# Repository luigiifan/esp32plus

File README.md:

# ESP32+ PROJECT

### I. Features
🔧 Fixes incorrect Boot Mode selection<br>
🔓 Compatible with <ins>ESP32 DevKit-V4 only</ins><br>
🔌 Stepdown Buck Converter MP1584 supports<br>
⚡ Includes 3.3V and 5V additional Power Expander<br>

### II. Technical Description
| Label  | Component  | I/O    | Switchable | Description |
| :------: | :-----: | :------: | :-----: | ----- |
| S1 | Pushbutton | GPIO 34 |  | Parallel with pull-up 10K Resistor to 3.3V |
| S2 | Pushbutton | GPIO 35 |  | Parallel with pull-up 10K Resistor to 3.3V |
| L1 | 3mm LED | GPIO 17 | ✅ | Series 330 ohm Resistor for current limiter, Toggle switch (IV) to enable |
| L2 | 3mm LED | GPIO 16 | ✅ | Series 330 ohm Resistor for current limiter, Toggle switch (III) to enable |
| L3 | 3mm LED | GPIO 4 | ✅ | Series 330 ohm Resistor for current limiter, Toggle switch (II) to enable |
| L4 | 3mm LED | GPIO 2 | ✅ | Series 330 ohm Resistor for current limiter, Toggle switch (I) to enable |
| SG1 | Buzzer DC | GPIO 32 | ✅ | Place (B) jumper on pins 1-2 to enable |
| DISP | OLED 128x32 | GPIO 21 (SDA) <br> GPIO 22 (SCL) | ✅ | Place (D) jumper on pins 1-2 to enable |
| C1 | Polar Capacitor | EN | | Determine ESP32 to FLASH mode upon power-up |

### III. Schematic 
🔗 [Download PDF](https://github.com/user-attachments/files/19268394/esp32_plus.pdf)

### IV. 3D Model & Drawing
<p>
  
🔗 [Download PDF](https://github.com/user-attachments/files/19269748/ESP32_PLUS_DRAWING.pdf)

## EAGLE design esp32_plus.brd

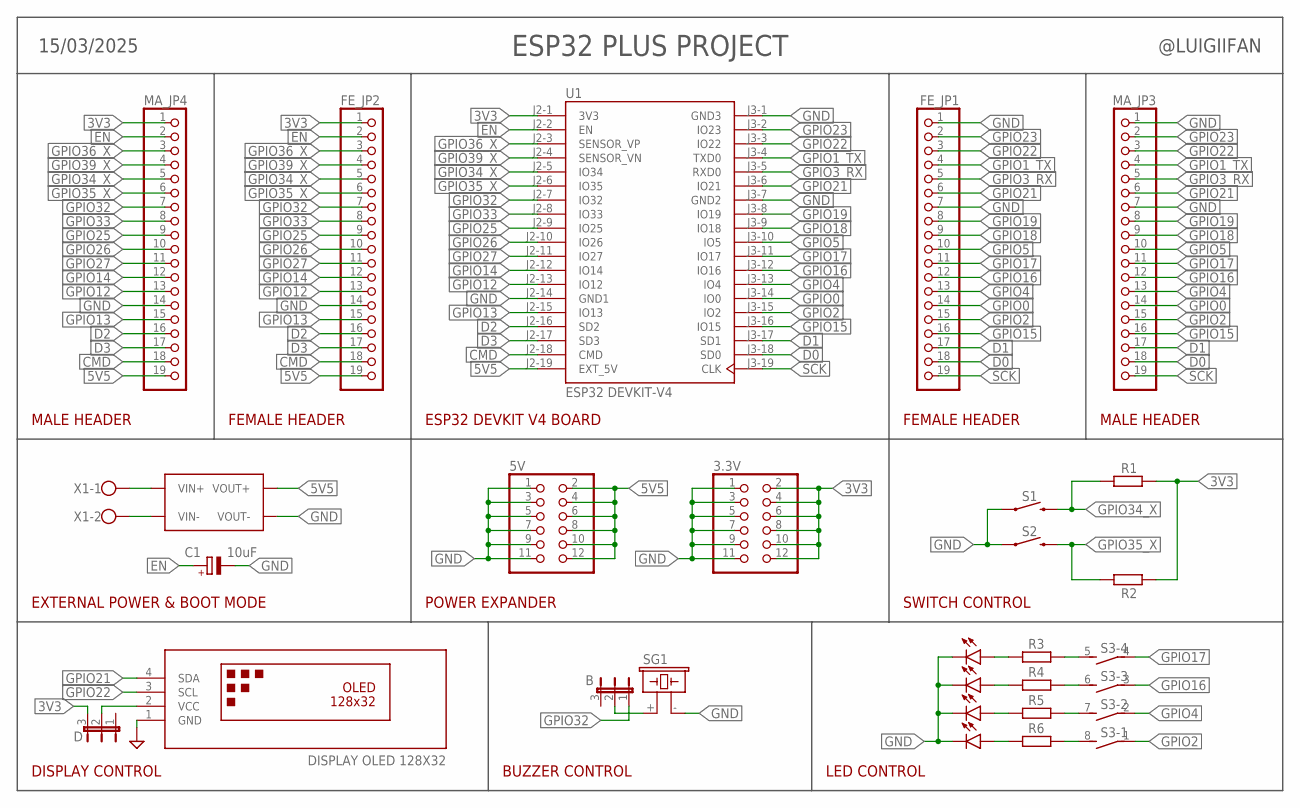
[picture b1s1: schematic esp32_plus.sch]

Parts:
3.3V, 5V: PINHD-2X6; 2X06
B: JP2E; JP2
C1: 10uF; E2,5-5
D: JP2E; JP2
FE_JP1, FE_JP2: PINHD-1X19; 1X19
L1, L2, L3, L4: LED3MM
MA_JP3, MA_JP4: PINHD-1X19; 1X19
MP1584: MP1584; DC-BRICK
R1, R2, R3, R4, R5, R6: R-EU_0207/10; 0207/10
S1, S2: MOMENTARY-SWITCH-SPST-PTH-6.0MM; TACTILE_SWITCH_PTH_6.0MM
S3: DS04E; DS-04
SG1: F/CM12P
U1: ESP32 DEVKIT-V4; MODULE_ESP32-DEVKITC-32D
U$1: DISPLAY OLED 128X32; DISPLAY-OLED-128X32
X1: W237-102

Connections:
3V3: 3.3V.2, 3.3V.4, 3.3V.6, 3.3V.8, 3.3V.10, 3.3V.12, D.3, FE_JP2.1, MA_JP4.1, R1.2, R2.2, U1.J2-1 (3V3)
5V5: 5V.2, 5V.4, 5V.6, 5V.8, 5V.10, 5V.12, FE_JP2.19, MA_JP4.19, MP1584.OUT1+ (VOUT+), MP1584.OUT2+ (VOUT+), U1.J2-19 (EXT_5V)
CMD: FE_JP2.18, MA_JP4.18, U1.J2-18 (CMD)
D0: FE_JP1.18, MA_JP3.18, U1.J3-18 (SD0)
D1: FE_JP1.17, MA_JP3.17, U1.J3-17 (SD1)
D2: FE_JP2.16, MA_JP4.16, U1.J2-16 (SD2)
D3: FE_JP2.17, MA_JP4.17, U1.J2-17 (SD3)
EN: C1.+, FE_JP2.2, MA_JP4.2, U1.J2-2 (EN)
GND: 3.3V.1, 3.3V.3, 3.3V.5, 3.3V.7, 3.3V.9, 3.3V.11, 5V.1, 5V.3, 5V.5, 5V.7, 5V.9, 5V.11, C1.-, FE_JP1.1, FE_JP1.7, FE_JP2.14, L1.K (C), L2.K (C), L3.K (C), L4.K (C), MA_JP3.1, MA_JP3.7, MA_JP4.14, MP1584.OUT1- (VOUT-), MP1584.OUT2- (VOUT-), S1.1, S2.1, SG1.- (2), U1.J2-14 (GND1), U1.J3-1 (GND3), U1.J3-7 (GND2), U$1.1 (GND)
GPIO0: FE_JP1.14, MA_JP3.14, U1.J3-14 (IO0)
GPIO1_TX: FE_JP1.4, MA_JP3.4, U1.J3-4 (TXD0)
GPIO2: FE_JP1.15, MA_JP3.15, S3.1, U1.J3-15 (IO2)
GPIO3_RX: FE_JP1.5, MA_JP3.5, U1.J3-5 (RXD0)
GPIO4: FE_JP1.13, MA_JP3.13, S3.2 (1), U1.J3-13 (IO4)
GPIO5: FE_JP1.10, MA_JP3.10, U1.J3-10 (IO5)
GPIO12: FE_JP2.13, MA_JP4.13, U1.J2-13 (IO12)
GPIO13: FE_JP2.15, MA_JP4.15, U1.J2-15 (IO13)
GPIO14: FE_JP2.12, MA_JP4.12, U1.J2-12 (IO14)
GPIO15: FE_JP1.16, MA_JP3.16, U1.J3-16 (IO15)
GPIO16: FE_JP1.12, MA_JP3.12, S3.3 (1), U1.J3-12 (IO16)
GPIO17: FE_JP1.11, MA_JP3.11, S3.4 (1), U1.J3-11 (IO17)
GPIO18: FE_JP1.9, MA_JP3.9, U1.J3-9 (IO18)
GPIO19: FE_JP1.8, MA_JP3.8, U1.J3-8 (IO19)
GPIO21: FE_JP1.6, MA_JP3.6, U1.J3-6 (IO21), U$1.4 (SDA)
GPIO22: FE_JP1.3, MA_JP3.3, U1.J3-3 (IO22), U$1.3 (SCL)
GPIO23: FE_JP1.2, MA_JP3.2, U1.J3-2 (IO23)
GPIO25: FE_JP2.9, MA_JP4.9, U1.J2-9 (IO25)
GPIO26: FE_JP2.10, MA_JP4.10, U1.J2-10 (IO26)
GPIO27: FE_JP2.11, MA_JP4.11, U1.J2-11 (IO27)
GPIO32: B.1, FE_JP2.7, MA_JP4.7, U1.J2-7 (IO32)
GPIO33: FE_JP2.8, MA_JP4.8, U1.J2-8 (IO33)
GPIO34_X: FE_JP2.5, MA_JP4.5, R1.1, S1.4 (2), U1.J2-5 (IO34)
GPIO35_X: FE_JP2.6, MA_JP4.6, R2.1, S2.4 (2), U1.J2-6 (IO35)
GPIO36_X: FE_JP2.3, MA_JP4.3, U1.J2-3 (SENSOR_VP)
GPIO39_X: FE_JP2.4, MA_JP4.4, U1.J2-4 (SENSOR_VN)
unnamed: D.2, U$1.2 (VCC)
unnamed: R4.2, S3.6 (2)
unnamed: R5.2, S3.7 (2)
unnamed: R6.2, S3.8 (2)
unnamed: R3.2, S3.5 (2)
unnamed: B.2, SG1.+ (1)
unnamed: L1.A, R3.1
unnamed: L2.A, R4.1
unnamed: L3.A, R5.1
unnamed: L4.A, R6.1
unnamed: MP1584.IN1+ (VIN+), MP1584.IN2+ (VIN+), X1.1
unnamed: MP1584.IN1- (VIN-), MP1584.IN2- (VIN-), X1.2
SCK: FE_JP1.19, MA_JP3.19, U1.J3-19 (CLK)

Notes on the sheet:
ESP32 DEVKIT V4 BOARD
FEMALE HEADER
MALE HEADER
ESP32 PLUS PROJECT
EXTERNAL POWER & BOOT MODE
POWER EXPANDER
SWITCH CONTROL
DISPLAY CONTROL
BUZZER CONTROL
LED CONTROL
15/03/2025
@LUIGIIFAN

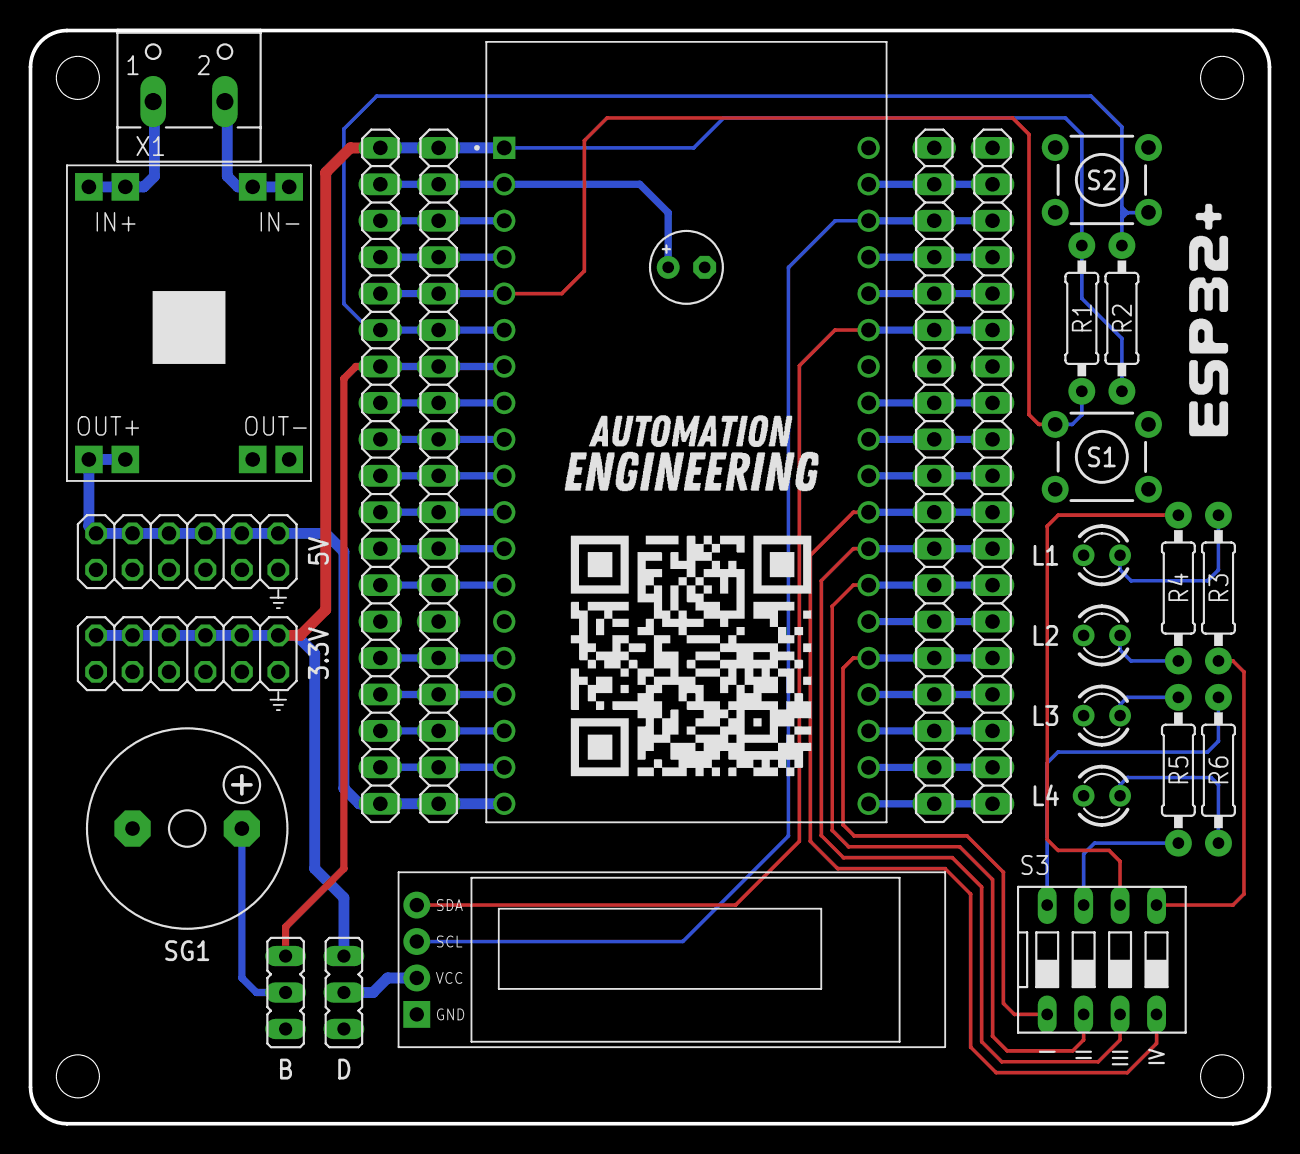
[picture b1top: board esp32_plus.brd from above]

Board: 2 copper layers, 86.4 x 76.2 mm, 27 parts (0 on the bottom side), 48 nets.

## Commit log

2025-04-02 Create LICENSE

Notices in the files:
parts and their libraries:
Sparkfun-SwitchEdit: Licensing: Creative Commons ShareAlike 4.0 International - https://creativecommons.org/licenses/by-sa/4.0
diy-modules_new: Released under the Creative Commons Attribution 4.0 International License: http://creativecommons.org/licenses/by/4.0
